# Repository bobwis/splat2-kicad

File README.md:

# splat2-kicad

Copy freerouter.jar to %appdata%\kicad  (needs java installation etc, not covered here)
Copy route.py to %appdata%\kicad\scripting\plugins  (create dir if doesn't exist)
Tools->External Plugins->Refresh

Preferences->Preferences->Pcbnew->Action Plugins
Select plugin
Click Show button

Now the hammer icon should be on the toolbar

To use
Export DSN to default file (do not rename)
Click the hammer

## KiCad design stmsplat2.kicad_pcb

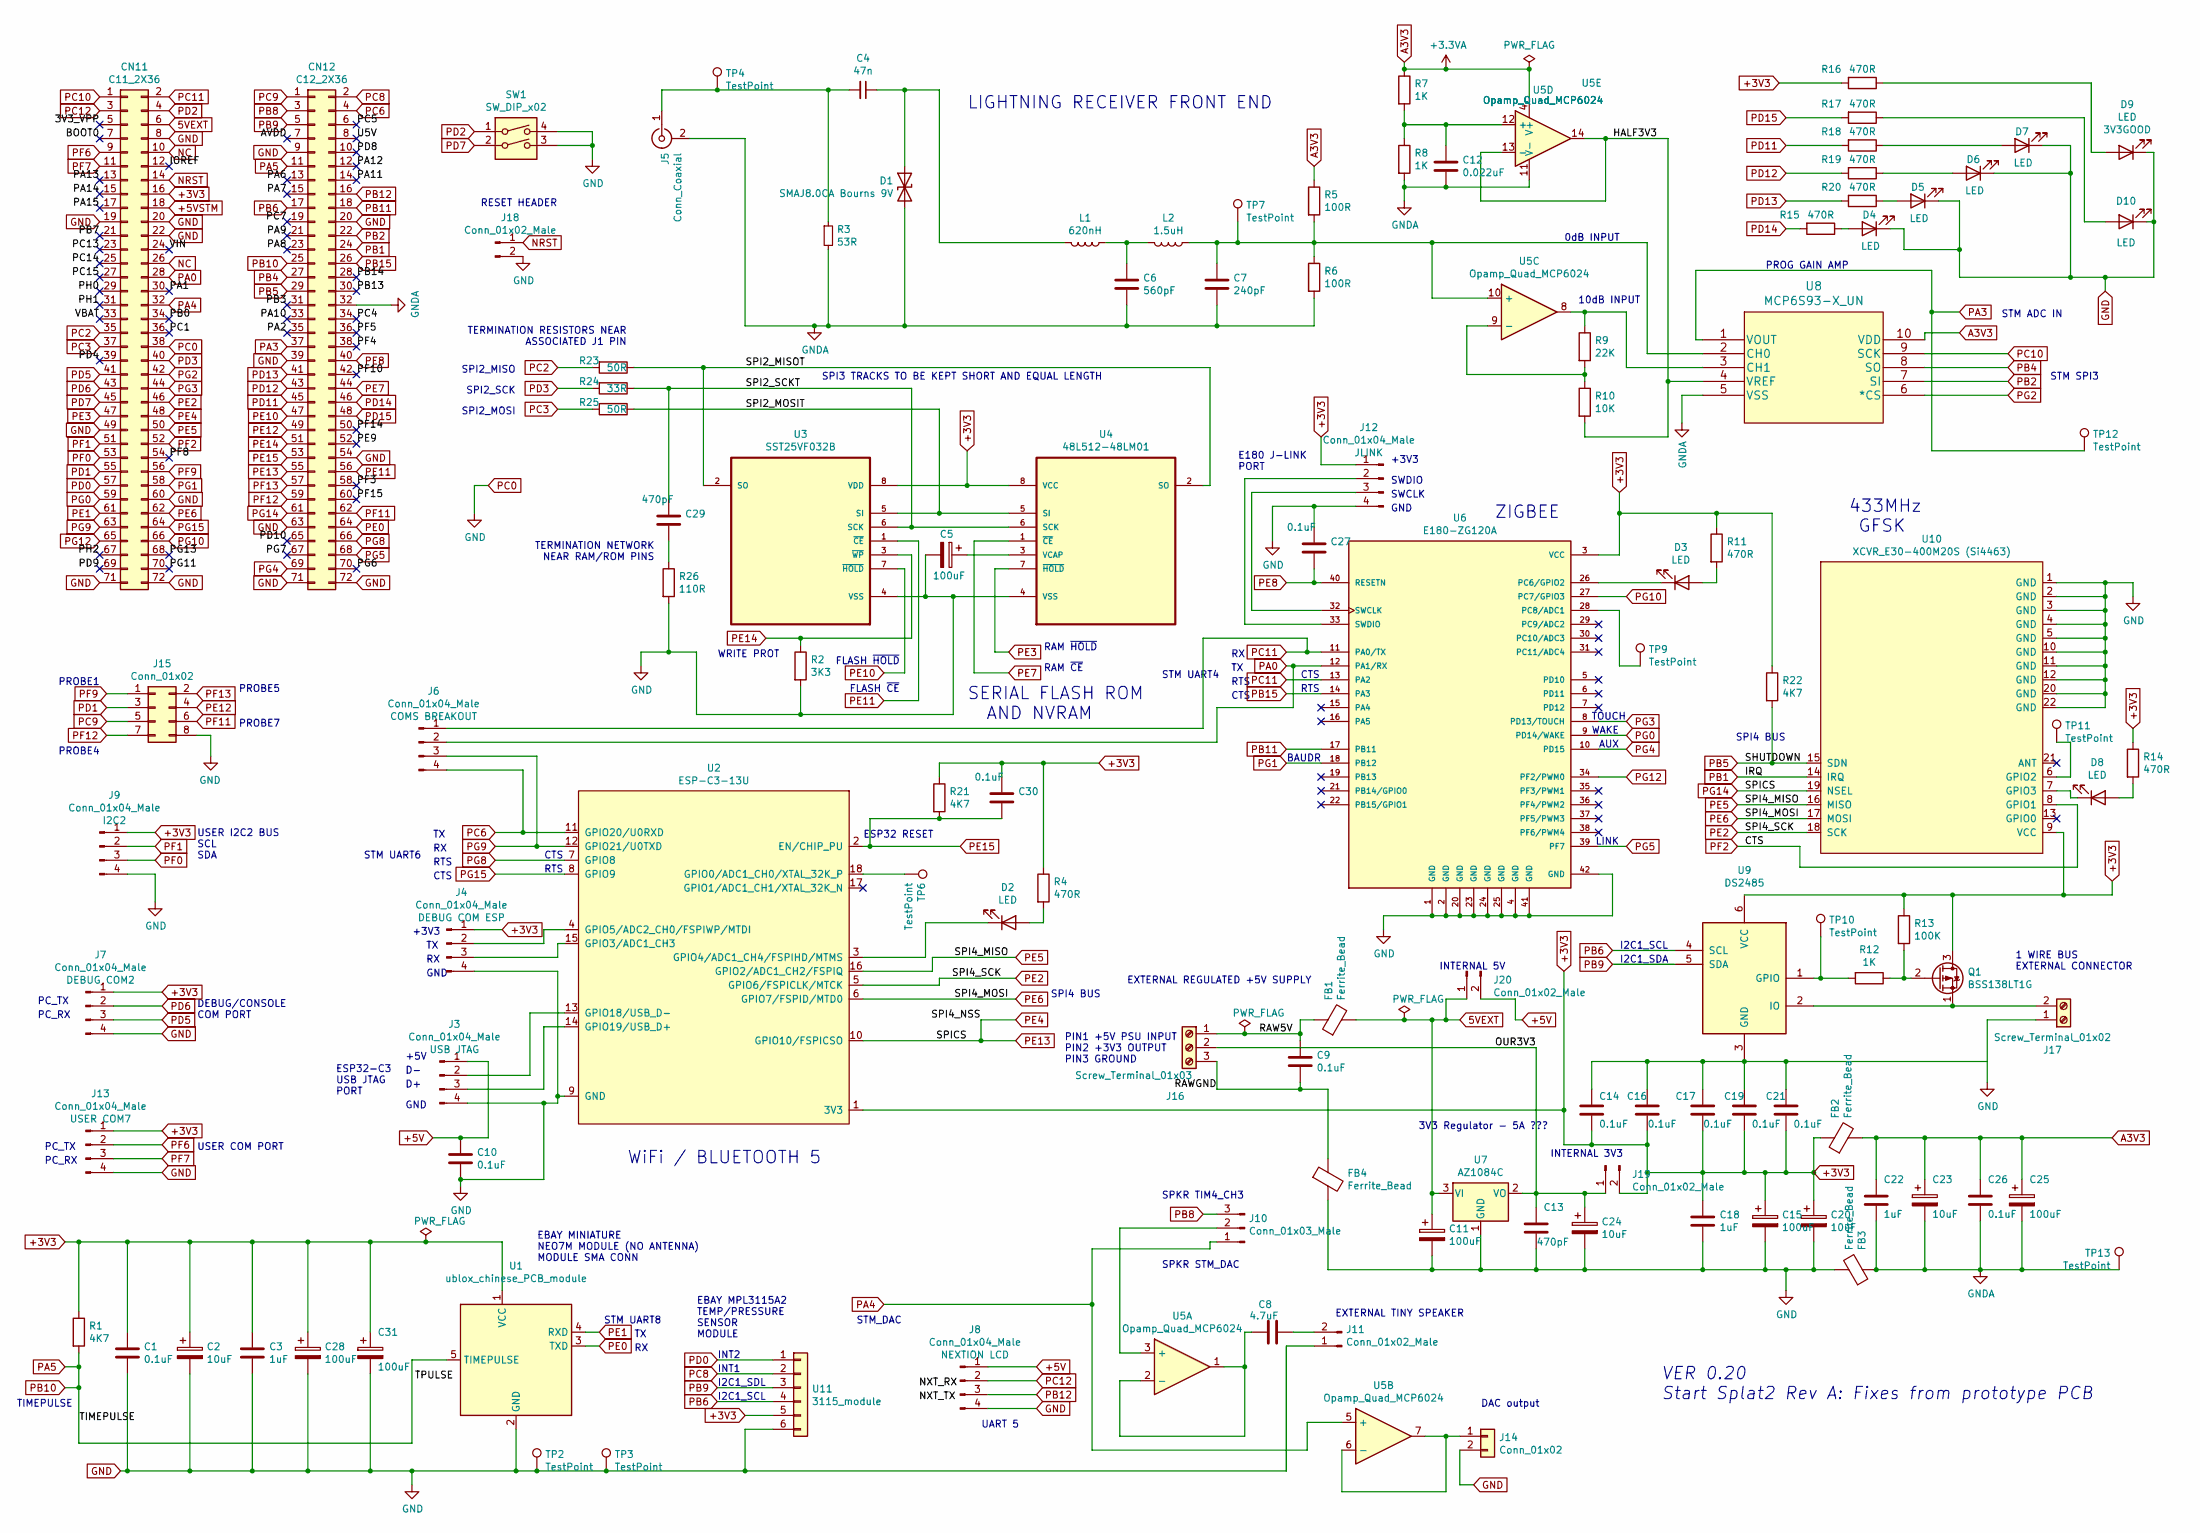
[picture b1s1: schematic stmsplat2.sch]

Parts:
C1, C10, C14, C16, C17, C19, C21, C26: 0.1uF; C_0805_2012Metric
C2, C20, C23, C24: 10uF; CP_Elec_5x5.4
C3, C18, C22: 1uF; C_0805_2012Metric
C4: 47n; C_1210_3225Metric_Pad1.42x2.65mm_HandSolder
C5, C11, C15, C25, C28, C31: 100uF; CP_Elec_6.3x7.7
C6: 560pF; C_0805_2012Metric_Pad1.15x1.40mm_HandSolder
C7: 240pF; C_0805_2012Metric_Pad1.15x1.40mm_HandSolder
C8: 4.7uF; C_0805_2012Metric
C9, C27, C30: 0.1uF; C_0805_2012Metric_Pad1.15x1.40mm_HandSolder
C12: 0.022uF; C_0805_2012Metric_Pad1.15x1.40mm_HandSolder
C13, C29: 470pF; C_0805_2012Metric_Pad1.15x1.40mm_HandSolder
CN11: C11_2X36; PinSocket_2x36_P2.54mm_Vertical
CN12: C12_2X36; PinSocket_2x36_P2.54mm_Vertical
D1: SMAJ8.0CA Bourns 9V; D_SMA_Handsoldering
D2, D3, D4, D5, D6, D7, D8, D9, D10: LED; LED_PLCC-2
FB1, FB2, FB3, FB4: Ferrite_Bead; L_0805_2012Metric
J3, J4, J6, J7, J8, J9, J12, J13: Conn_01x04_Male; PinHeader_1x04_P2.54mm_Vertical
J5: Conn_Coaxial; SMA_Amphenol_132134-11_Vertical
J10: Conn_01x03_Male; PinHeader_1x03_P2.54mm_Vertical
J11, J18, J19, J20: Conn_01x02_Male; PinHeader_1x02_P2.54mm_Vertical
J14: Conn_01x02; PinHeader_1x02_P2.54mm_Vertical
J15: Conn_01x02; PinHeader_2x04_P2.54mm_Vertical
J16: Screw_Terminal_01x03; TerminalBlock_Altech_AK300-3_P5.00mm
J17: Screw_Terminal_01x02; TerminalBlock_Altech_AK300-2_P5.00mm
L1: 620nH; L_1210_3225Metric_Pad1.42x2.65mm_HandSolder
L2: 1.5uH; L_1210_3225Metric_Pad1.42x2.65mm_HandSolder
Q1: BSS138LT1G; SOT-23
R1, R21, R22: 4K7; R_0805_2012Metric
R2: 3K3; R_0805_2012Metric
R3: 53R; C_1210_3225Metric_Pad1.42x2.65mm_HandSolder
R4, R11, R14, R15, R16, R17, R18, R19, R20: 470R; R_0805_2012Metric
R5, R6: 100R; R_0805_2012Metric
R7, R8, R12: 1K; R_0805_2012Metric
R9: 22K; R_0805_2012Metric
R10: 10K; R_0805_2012Metric
R13: 100K; R_0805_2012Metric
R23, R25: 50R; R_0805_2012Metric
R24: 33R; R_0805_2012Metric
R26: 110R; R_0805_2012Metric
SW1: SW_DIP_x02; SW_DIP_SPSTx02_Slide_Omron_A6S-210x_W8.9mm_P2.54mm
TP2, TP3, TP4, TP6, TP7, TP9, TP10, TP11, TP12, TP13: TestPoint; TestPoint_Loop_D1.80mm_Drill1.0mm_Beaded
U1: ublox_chinese_PCB_module; NEO7_GPS_MODULE
U2: ESP-C3-13U; ESP-C3-13
U3: SST25VF032B; SOIC127P790X216-8N
U4: 48L512-48LM01; SOIC127P790X216-8N
U5: Opamp_Quad_MCP6024; SOIC-14_3.9x8.7mm_P1.27mm
U6: E180-ZG120A; XCVR_E180-ZG120A; PARTREV 1.2
U7: AZ1084C; TO-252-3_TabPin2
U8: MCP6S93-X_UN; MSOP-10_3x3mm_P0.5mm
U9: DS2485; DFN-6-1EP_3x3mm_P1mm_EP1.5x2.4mm
U10: XCVR_E30-400M20S (Si4463); XCVR_E30-400M20S
U11: 3115_module; 3115_PRESSURE_MODULE

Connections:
5VEXT: C11.1, CN11.6, FB1.2, J20.1, U7.3 (VI)
+3V3: C1.1, C2.1, C3.1, C14.2, C15.1, C16.2, C17.2, C18.1, C19.2, C20.1, C21.2, C28.1, C30.1, C31.1, CN11.16, FB2.1, J4.1, J7.1, J9.1, J12.1, J13.1, J19.2, Q1.3 (D), R1.1, R4.1, R11.1, R13.1, R14.1, R16.2, R21.1, R22.1, U1.1 (VCC), U2.1 (3V3), U3.8 (VDD), U4.8 (VCC), U6.3 (VCC), U9.6 (VCC), U10.9 (VCC), U11.5
+5V: C10.1, J3.1, J8.1, J20.2
+5VSTM: CN11.18
/3V3_VPP: CN11.5
/AVDD: CN12.7
/BOOT0: CN11.7
/HALF3V3: R10.2, U5.13 (-), U5.14, U8.4 (VREF)
/IOREF: CN11.12
/OUR3V3: C13.1, C24.1, J16.2, J19.1, U7.2 (VO)
/PA1: CN11.30
/PA2: CN12.35
/PA6: CN12.13
/PA7: CN12.15
/PA8: CN12.23
/PA9: CN12.21
/PA10: CN12.33
/PA11: CN12.14
/PA12: CN12.12
/PA13: CN11.13
/PA14: CN11.15
/PA15: CN11.17
/PB0: CN11.34
/PB3: CN12.31
/PB7: CN11.21
/PB13: CN12.30
/PB14: CN12.28
/PC1: CN11.36
/PC4: CN12.34
/PC5: CN12.6
/PC7: CN12.19
/PC13: CN11.23
/PC14: CN11.25
/PC15: CN11.27
/PD4: CN11.39
/PD8: CN12.10
/PD9: CN11.69
/PD10: CN12.65
/PE9: CN12.52
/PF3: CN12.58
/PF4: CN12.38
/PF5: CN12.36
/PF8: CN11.54
/PF10: CN12.42
/PF14: CN12.50
/PF15: CN12.60
/PG6: CN12.70
/PG7: CN12.67
/PG11: CN11.70
/PG13: CN11.68
/PH0: CN11.29
/PH1: CN11.31
/PH2: CN11.67
/RAW5V: C9.1, FB1.1, J16.1
/RAWGND: C9.2, FB4.1, J16.3
/SPI2_MISOT: R23.1, U3.2 (SO), U4.2 (SO)
/SPI2_MOSIT: R25.1, U3.5 (SI), U4.5 (SI)
/SPI2_SCKT: C29.1, R24.1, U3.6 (SCK), U4.6 (SCK)
/U5V: CN12.8
/VBAT: CN11.33
/VIN: CN11.24
A3V3: C22.1, C23.1, C25.1, C26.1, FB2.2, R5.1, R7.1, U5.4 (V+), U8.10 (VDD)
GND: C1.2, C2.2, C3.2, C5.2, C10.2, C11.2, C13.2, C14.1, C15.2, C16.1, C17.1, C18.2, C19.1, C20.2, C21.1, C24.2, C27.1, C28.2, C31.2, CN11.8, CN11.19, CN11.20, CN11.22, CN11.38, CN11.49, CN11.60, CN11.71, CN11.72, CN12.9, CN12.20, CN12.39, CN12.54, CN12.63, CN12.71, CN12.72, D4.1 (K), D5.1 (K), D6.1 (K), D7.1 (K), D9.1 (K), D10.1 (K), FB3.2, FB4.2, J3.4, J4.4, J7.4, J8.4, J9.4, J11.1, J12.4, J13.4, J14.2, J15.8, J17.1, J18.2, R2.2, R26.2, SW1.3, SW1.4, TP2.1, TP3.1, U1.2 (GND), U2.9 (GND), U3.4 (VSS), U4.4 (VSS), U6.1 (GND), U6.2 (GND), U6.4 (GND), U6.20 (GND), U6.23 (GND), U6.24 (GND), U6.25 (GND), U6.41 (GND), U6.42 (GND), U7.1 (GND), U9.3 (GND), U10.1 (GND), U10.2 (GND), U10.3 (GND), U10.4 (GND), U10.5 (GND), U10.10 (GND), U10.11 (GND), U10.12 (GND), U10.20 (GND), U10.22 (GND), U11.6
GNDA: C6.2, C7.2, C12.2, C22.2, C23.2, C25.2, C26.2, CN12.32, D1.2 (A2), FB3.1, J5.2 (Ext), R3.2, R6.2, R8.2, TP13.1, U5.11 (V-), U8.5 (VSS); also elsewhere on the board
NC: CN11.10, CN11.26
NRST: CN11.14, J18.1
unnamed: C4.1, D1.1 (A1), L1.2
unnamed: C4.2, J5.1 (In), R3.1, TP4.1
unnamed: C5.1, U4.3 (VCAP)
unnamed: C6.1, L1.1, L2.2
unnamed: C7.1, L2.1, R5.2, R6.1, TP7.1, U5.10 (+), U8.2 (CH0)
unnamed: C8.1, U5.1, U5.2 (-)
unnamed: C8.2, J11.2
unnamed: C12.1, R7.2, R8.1, U5.12 (+)
unnamed: C29.2, R26.1
unnamed: D2.1 (K), U2.3 (GPIO4/ADC1_CH4/FSPIHD/MTMS)
unnamed: D2.2 (A), R4.2
unnamed: D3.1 (K), U6.26 (PC6/GPIO2)
unnamed: D3.2 (A), R11.2
unnamed: D4.2 (A), R15.1
unnamed: D5.2 (A), R20.1
unnamed: D6.2 (A), R19.1
unnamed: D7.2 (A), R18.1
unnamed: D8.1 (K), U10.7 (GPIO3)
unnamed: D8.2 (A), R14.2
unnamed: D9.2 (A), R16.1
unnamed: D10.2 (A), R17.1
unnamed: J3.2, U2.13 (GPIO18/USB_D-)
unnamed: J3.3, U2.14 (GPIO19/USB_D+)
unnamed: J4.2, U2.4 (GPIO5/ADC2_CH0/FSPIWP/MTDI)
unnamed: J4.3, U2.15 (GPIO3/ADC1_CH3)
unnamed: J10.2, U5.3 (+)
unnamed: J12.2, U6.33 (SWDIO)
unnamed: J12.3, U6.32 (SWCLK)
unnamed: J14.1, U5.6 (-), U5.7
unnamed: J17.2, Q1.1 (S), U9.2 (IO)
unnamed: Q1.2 (G), R12.1, R13.2
unnamed: R9.1, U5.8, U8.3 (CH1)
unnamed: R9.2, R10.1, U5.9 (-)
unnamed: R12.2, TP10.1, U9.1 (GPIO)
unnamed: TP6.1, U2.18 (GPIO0/ADC1_CH0/XTAL_32K_P)
unnamed: TP9.1, U6.28 (PC8/ADC1)
unnamed: TP11.1, U10.6 (GPIO2)
PA0: CN11.28, J6.2, U6.12 (PA1/RX)
PA3: CN12.37, TP12.1, U8.1 (VOUT)
PA4: CN11.32, J10.1, U5.5 (+)
PA5: CN12.11, CN12.25, R1.2, U1.5 (TIMEPULSE)
PB1: CN12.24, U10.14 (IRQ)
PB2: CN12.22, U8.7 (SI)
PB4: CN12.27, U8.8 (SO)
PB5: CN12.29, R22.2, U10.15 (SDN)
PB6: CN12.17, U9.4 (SCL), U11.4
PB8: CN12.3, J10.3
PB9: CN12.5, U9.5 (SDA), U11.3
PB11: CN12.18, U6.17 (PB11)
PB12: CN12.16, J8.3
PB15: CN12.26, U6.14 (PA3)
PC2: CN11.35, R23.2
PC3: CN11.37, R25.2
PC6: CN12.4, J6.4, U2.11 (GPIO20/U0RXD)
PC8: CN12.2, U11.2
PC9: CN12.1, J15.5
PC10: CN11.1, U8.9 (SCK)
PC11: CN11.2, J6.1, U6.11 (PA0/TX), U6.13 (PA2)
PC12: CN11.3, J8.2
PD0: CN11.57, U11.1
PD1: CN11.55, J15.3
PD2: CN11.4, SW1.1
PD3: CN11.40, R24.2
PD5: CN11.41, J7.3
PD6: CN11.43, J7.2
PD7: CN11.45, SW1.2
PD11: CN12.45, R18.2
PD12: CN12.43, R19.2
PD13: CN12.41, R20.2
PD14: CN12.46, R15.2
PD15: CN12.48, R17.2
PE0: CN12.64, U1.3 (TXD)
PE1: CN11.61, U1.4 (RXD)
PE2: CN11.46, U2.5 (GPIO6/FSPICLK/MTCK), U10.18 (SCK)
PE3: CN11.47, U4.7 (~HOLD)
PE5: CN11.50, U2.16 (GPIO2/ADC1_CH2/FSPIQ), U10.16 (MISO)
PE6: CN11.62, U2.6 (GPIO7/FSPID/MTD0), U10.17 (MOSI)
PE7: CN12.44, U4.1 (~CE)
PE8: C27.2, CN12.40, U6.40 (RESETN)
PE10: CN12.47, U3.7 (~HOLD)
PE11: CN12.56, U3.1 (~CE)
PE12: CN12.49, J15.4
PE13: CN11.48, CN12.55, CN12.61, U2.10 (GPIO10/FSPICSO), U10.19 (NSEL)
PE14: CN12.51, R2.1, U3.3 (~WP)
PE15: C30.2, CN12.53, R21.2, U2.2 (EN/CHIP_PU)
PF0: CN11.53, J9.3
PF1: CN11.51, J9.2
PF2: CN11.52, U10.8 (GPIO1)
PF6: CN11.9, J13.2
PF7: CN11.11, J13.3
PF9: CN11.56, J15.1
PF11: CN12.62, J15.6
PF12: CN12.59, J15.7
PF13: CN12.57, J15.2
PG0: CN11.59, U6.9 (PD14/WAKE)
PG1: CN11.58, U6.18 (PB12)
PG2: CN11.42, U8.6 (*CS)
PG3: CN11.44, U6.8 (PD13/TOUCH)
PG4: CN12.69, U6.10 (PD15)
PG5: CN12.68, U6.39 (PF7)
PG8: CN12.66, U2.7 (GPIO8)
PG9: CN11.63, J6.3, U2.12 (GPIO21/U0TXD)
PG10: CN11.66, U6.27 (PC7/GPIO3)
PG12: CN11.65, U6.34 (PF2/PWM0)
PG15: CN11.64, U2.8 (GPIO9)

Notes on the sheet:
STM UART8
I2C1_SCL
I2C1_SDA
RTS
CTS
ESP32 RESET
1 WIRE BUS EXTERNAL CONNECTOR
DAC output
EBAY MPL3115A2 TEMP/PRESSURE SENSOR MODULE
I2C1_SDL
UART 5
ESP32-C3 USB JTAG PORT
SPI2_SCK
SPI2_MOSI
SPI2_MISO
SPI3 TRACKS TO BE KEPT SHORT AND EQUAL LENGTH
STM_DAC
SPKR TIM4_CH3
SPKR STM_DAC
SPI4 BUS
STM UART6
PC_RX
PC_TX
+3V3
GND
TIMEPULSE
+5V
RAM ~HOLD
RAM ~CE
FLASH ~CE
FLASH ~HOLD
STM UART4
E180 J-LINK PORT
SWDIO
SWCLK
RTS
BAUDR
AUX
WAKE
TOUCH

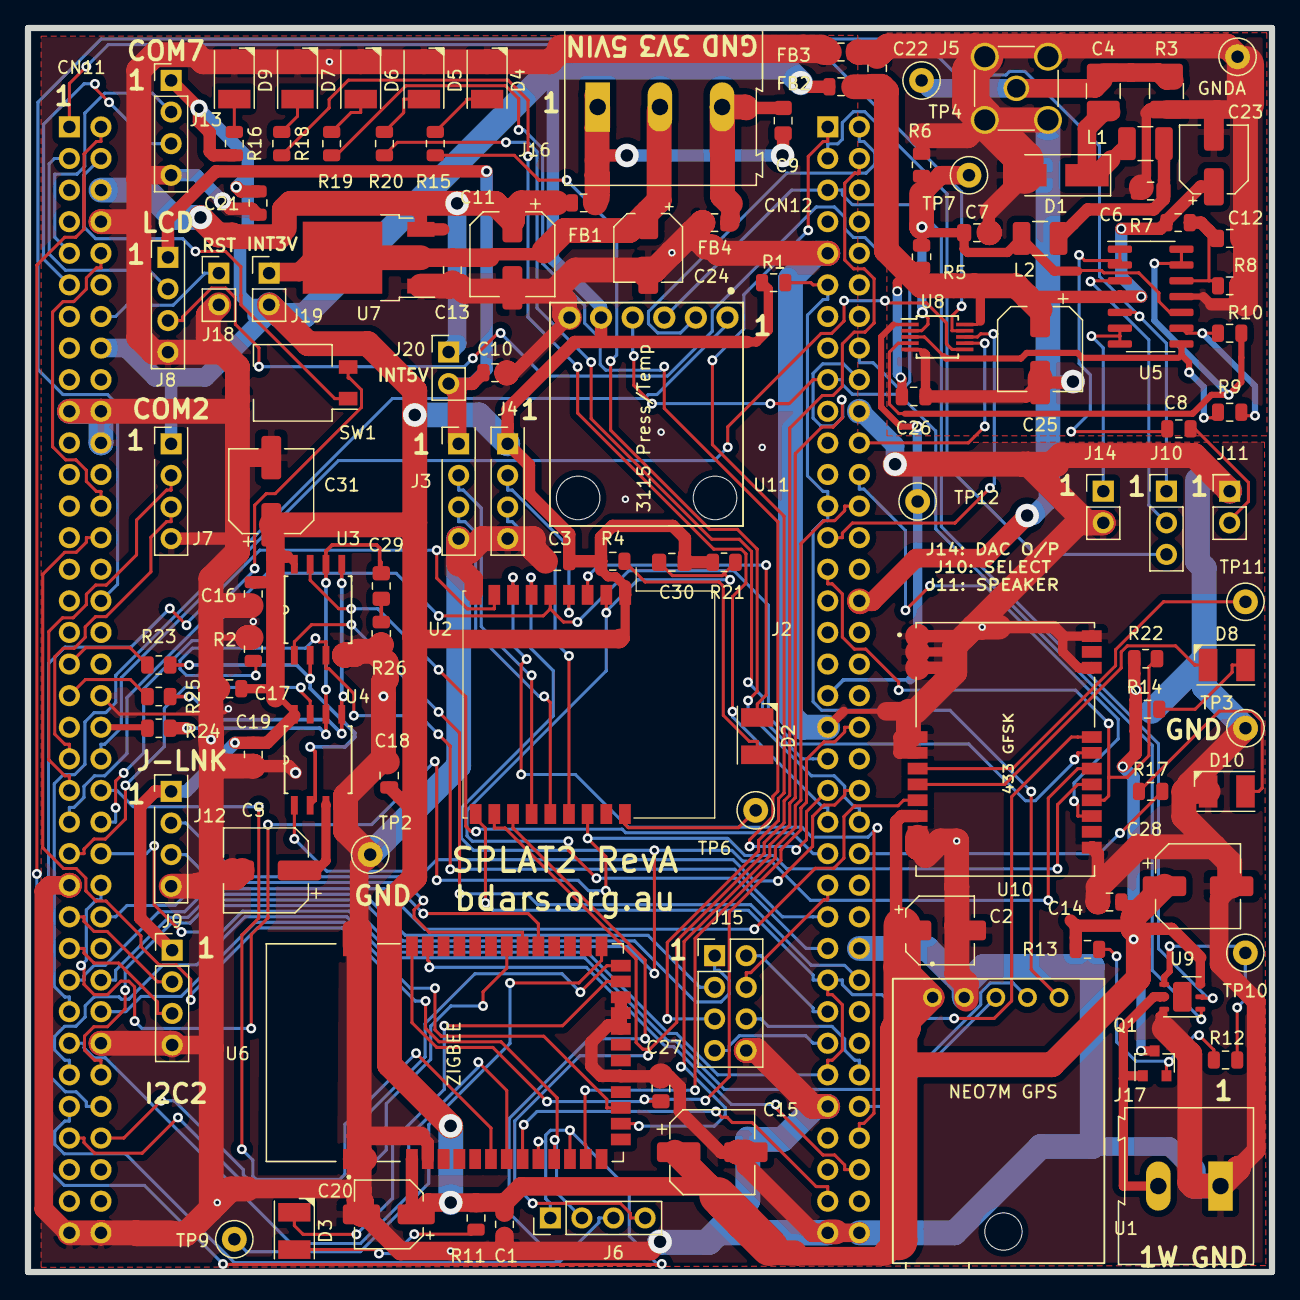
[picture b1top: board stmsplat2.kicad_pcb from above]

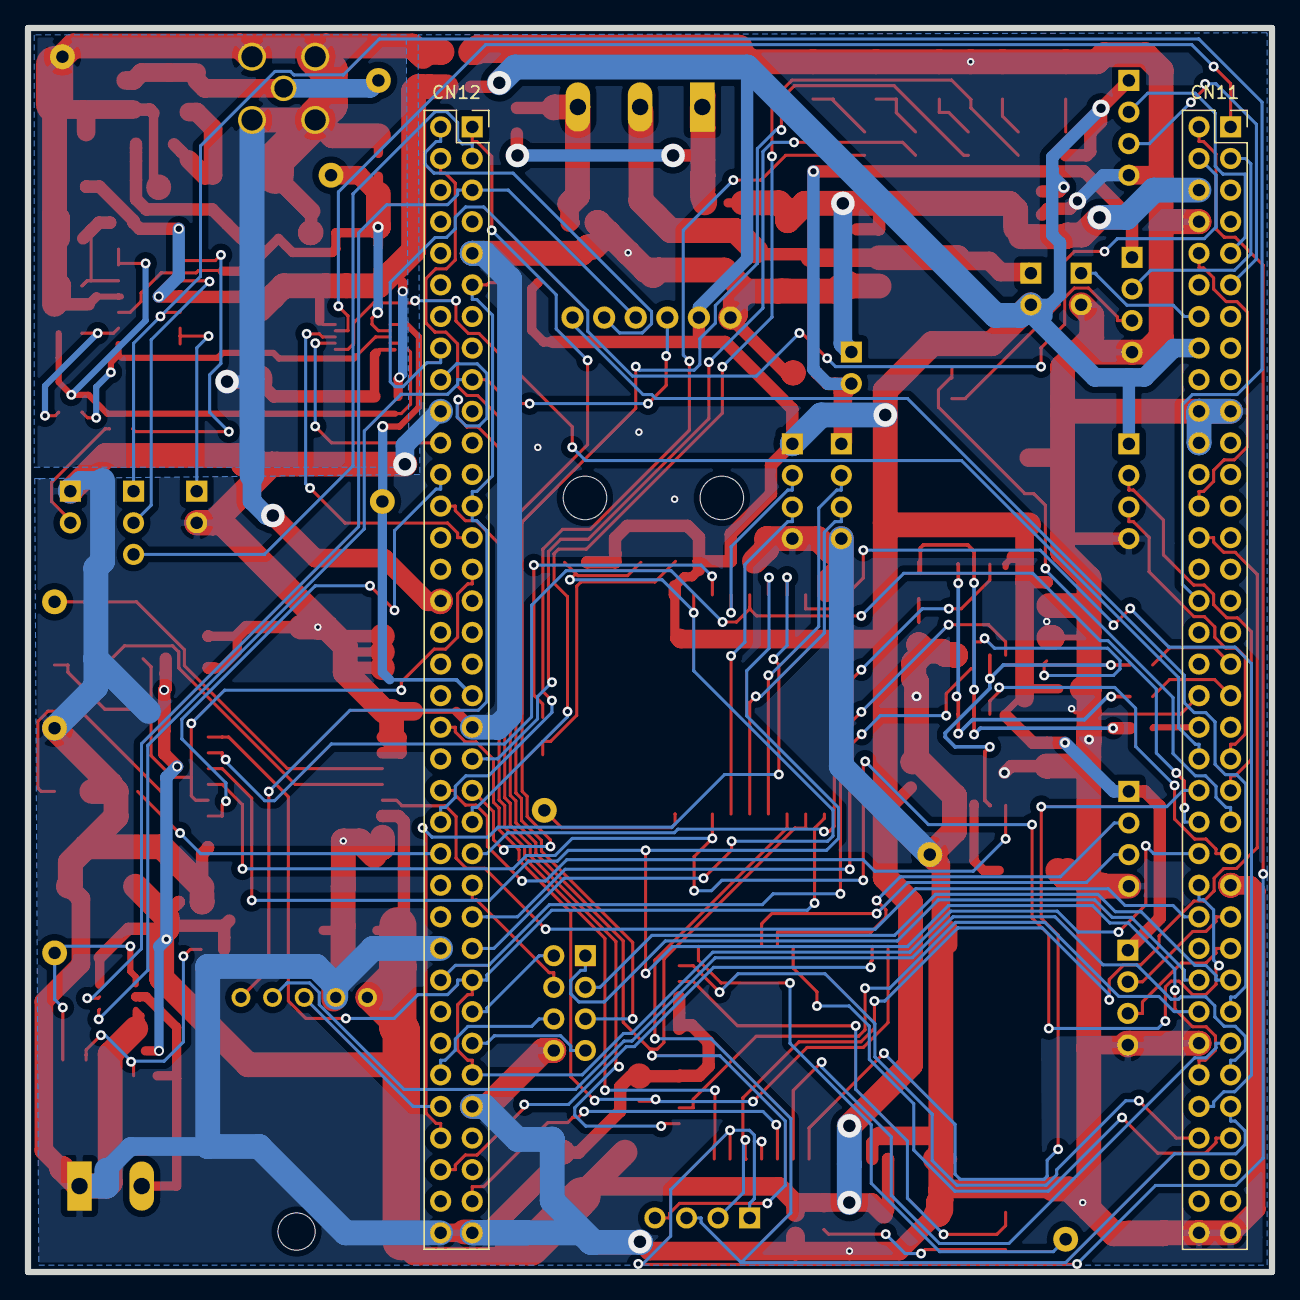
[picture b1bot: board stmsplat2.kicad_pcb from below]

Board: 2 copper layers, 100.0 x 100.0 mm, 116 parts (2 on the bottom side), 120 nets.

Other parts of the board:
GNDA: TestPoint; TestPoint_Loop_D1.80mm_Drill1.0mm_Beaded

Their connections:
GNDA: GNDA.1; also elsewhere on the board

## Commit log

2021-11-17 Added kicad files
2021-11-18 Connector mods
    Changed power rails to work with onboard/offboard 5V supply
    Added user header for GPIO signals / Probes
    Added User UART and I2C header
    checked 72 pin connectors and signal names to devices
    **STILL NEEDS ERC and FOOTPRINT updates *** After Supply sourcing checks
2021-11-18 changed all 0603 footprints to 0805 in the schematic
2021-11-18 forgot to bump Sch ver to 0.04
2021-11-18 test change at David's
2021-11-18 deleted old splat1 pcb outline
2021-11-22 ERC report
2021-11-23 ERC check resolution, resolved empty / unused nets
2021-11-23 0 ERC - modified custom lib to clarify pin types
2021-11-23 Rejigged library
2021-11-24 Corrected typo
2021-11-24 Removed references to spatboard
2021-11-24 Removed more spatboard references
2021-11-24 Footprints to new format and all link to the custom splat2footprints library
    VER 0.07: ALMOST FROZEN - pretty library footprints,
    3115 footprint unfinished and
    changed from J to U designation on SCH
    Added com breakout header
    labeled raw5v and rawgnd
2021-11-24 updated 3115 module footprint and on the PCB
2021-11-24 Thrown down the components and made a 100x100 outline to see how well it might fit
2021-11-26 Ver 0.9. Initial PCB placement attempt. Some footprints changed
2021-11-26 Spectra Export
2021-11-26 improved placement]
2021-11-27 Added a few passives in sch. Library update may not be good? Placement tweaks.
2021-11-27 updated DSN
2021-11-28 Few footprints changes, placement changes, initial routing success
    SCH: 0.11 (now feature frozen)
    PCB: Placement 1.2
    PCB Routed 1.0
    The unrouted pcb is also in this folder
2021-11-28 I think this is the correct .dsn file used to generate the last PCB?
2021-11-29 SPI2<->SPI3. Different placement. Routed, but may have other errors
    Swapped SPI2 and SPI3 and have added termination for SPI2 (which may not be needed)/ Moved RAM/ROM components close to the connector
2021-11-29 added BOM and removed old pcb
2021-11-29 Update readme and add default plugin script
2021-11-29 Routing attempt
2021-11-30 speed up routing
2021-11-30 placement candidate 2 with routed candidate 1.0
2021-12-01 better placement, more handrouting, re-done power area etc
    A few more passive comps added including dil switch
2021-12-04 PCB Layout finished. Gerbers produced, needs checking
    Ready to send off to PCB house?
2021-12-06 U8 pads adjustment. PC0->GND, minor silkscreen tweaks
2021-12-06 more silkscreen tweaks
2021-12-07 Updated bom
2021-12-20 Correct the PowerConn Pin assignments
    these were changed to facilitate easier PCB layout
2021-12-20 Forgot to bump Schematic version
    This is now bumped to Ver 0.18
2022-01-10 Splat2 Revision A. Work-in-progress
2022-01-11 Routed but needs checking
2022-01-11 Copper pours added
2022-01-15 Sent off for PCB manufacture
